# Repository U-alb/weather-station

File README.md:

# Weather Station

Rust-powered environmental monitoring station

## Description

The project builds a weather station which provides real-time weather data on an external display and web interface

## Motivation

Building a Raspberry Pi Pico W weather station with embassy-rs combined my interest in embedded systems with a chance to explore networking. It allows me to learn sensor interaction and data processing. Integrating a web interface adds a network layer, enabling real-time data display and opening doors for future functionalities like remote monitoring.

## Hardware

We will use a BME280 in order to gather environmental data. The Pico will process this gathered data in order to print meaningful graphics on the provided display. We will also use several push buttons in order to switch between the available data

### Bill of Materials

| Device | Usage | Price |
|--------|--------|-------|
| [Raspberry Pi Pico WH](https://www.raspberrypi.com/documentation/microcontrollers/raspberry-pi-pico.html) | The microcontroller | [56 RON](https://ardushop.ro/ro/home/2819-raspberry-pi-pico-wh.html) |
| [BME280](https://www.bosch-sensortec.com/products/environmental-sensors/humidity-sensors-bme280/) | Temperature, pressure and humidity sensor | [74 RON](https://www.optimusdigital.ro/ro/senzori-senzori-de-presiune/5649-modul-senzor-barometric-de-presiune-bme280.html) |
| [LED Display](https://ardushop.ro/8014-thickbox_default/modul-lcd-spi-128x160.webp) | Display | [39 RON](https://ardushop.ro/ro/home/2818-modul-lcd-spi-128x160.html) |
| [Breadboard](https://www.yamanelectronics.com/wp-content/uploads/2020/06/basics-of-breadboard.webp) | The physical base of the project | [10 RON](https://www.optimusdigital.ro/ro/prototipare-breadboard-uri/8-breadboard-830-points.html) |
| [Jumper Wires](http://www.atomsindustries.com/assets/images/items/1075/1075.webp) | For connecting all the different components | [7 RON](https://www.optimusdigital.ro/ro/fire-fire-mufate/886-set-fire-tata-tata-40p-15-cm.html) |
| [Push buttons](https://ardushop.ro/655-thickbox_default/buton-mic-push-button-trough-hole.webp) | For switching info on the screen| [0.36 RON each / 1.5 RON total](https://www.optimusdigital.ro/ro/butoane-i-comutatoare/1119-buton-6x6x6.html)

## Software

| Library | Description | Usage |
|---------|-------------|-------|
| [embassy-rp](https://github.com/embassy-rs/embassy/tree/main/embassy-rp) | The embassy-rp HAL targets the Raspberry Pi RP2040 microcontroller. The HAL implements both blocking and async APIs for many peripherals. |  The utilised HAL  |
| [embassy-sync](https://github.com/embassy-rs/embassy/tree/main/embassy-sync) | An Embassy project| Used for mutexes and sending and receiving data over channels |
| [embassy-time](https://github.com/embassy-rs/embassy/tree/main/embassy-time) | An Embassy project | Used for organising the flow of the program via Timer:: |
| [embassy-embedded-hal](https://github.com/embassy-rs/embassy/tree/main/embassy-embedded-hal) | Collection of utilities to use `embedded-hal` and `embedded-storage` traits with Embassy. | Used for the SPI config |
| [embassy-futures](https://github.com/embassy-rs/embassy/tree/main/embassy-futures) | An Embassy project | Used for working with futures during asynchronous development |
| [st7789](https://github.com/almindor/st7789) | Display driver for ST7789 | Used for the display |
| [embedded-graphics](https://github.com/embedded-graphics/embedded-graphics) | 2D graphics library | Used for drawing to the display |

## Links

1. [Idea](https://www.hackster.io/jotrinelectronics/building-a-weather-station-with-raspberry-pi-pico-rp2040-9d5cbb)
2. [Arduino BME280 Library (not Rust, but it was useful as a conceptual insight)](https://github.com/finitespace/BME280)

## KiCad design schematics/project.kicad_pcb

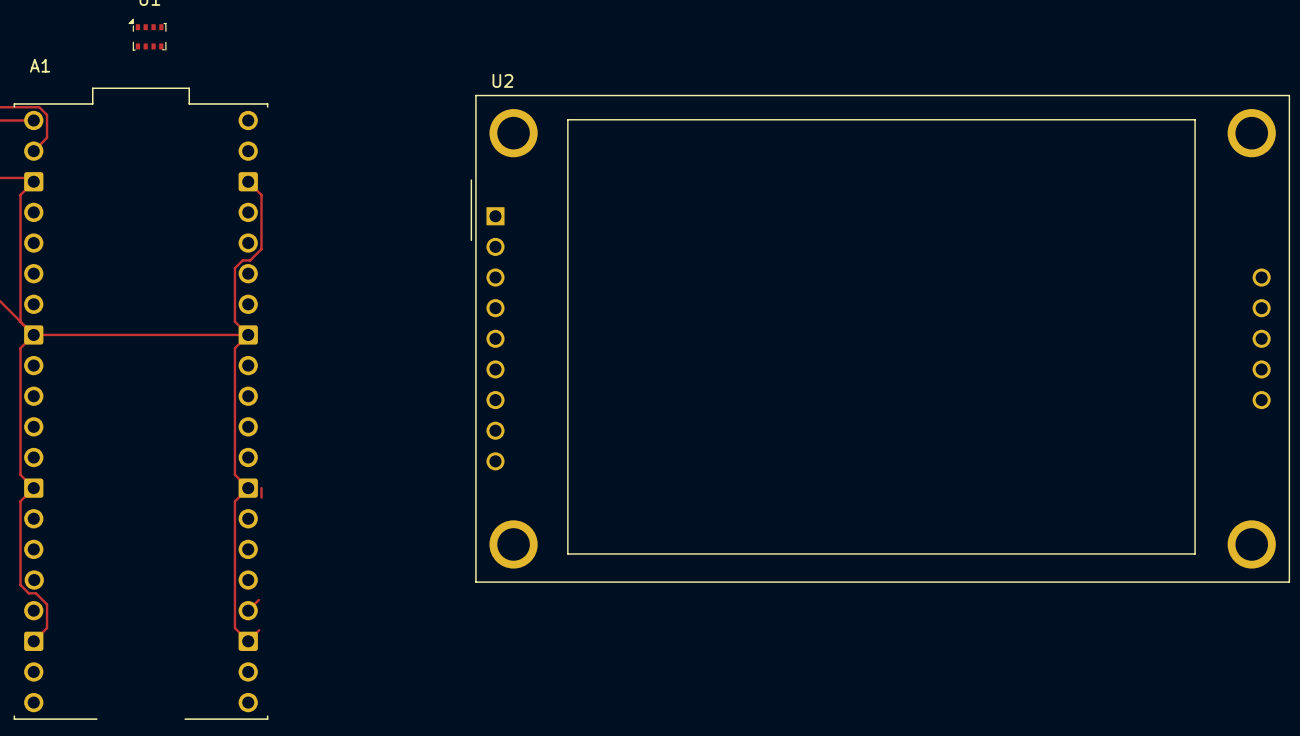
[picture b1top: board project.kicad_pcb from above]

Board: 2 copper layers, 3 parts (0 on the bottom side), 11 nets.

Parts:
A1: SC0918; MODULE_SC0918
U1: BMP280; Bosch_LGA-8_2x2.5mm_P0.65mm_ClockwisePinNumbering
U2: CR2013-MI2120

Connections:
+3V3: A1.36 (3V3_OUT), U1.6 (VDDIO), U1.8 (VDD), U2.1 (VCC), U2.8 (LED)
GND: A1.3 (GND), A1.8 (GND), A1.13 (GND), A1.18 (GND), A1.23 (GND), A1.28 (GND), A1.33 (AGND), A1.38 (GND), U1.1 (GND), U1.7 (GND), U2.2 (GND)
unnamed: A1.1 (GP0), U2.4 (RESET)
unnamed: A1.5 (GP3), U1.2 (CSB)
unnamed: A1.6 (GP4), U2.9 (MISO)
unnamed: A1.11 (GP8), U1.5 (SDO)
unnamed: A1.14 (GP10), U1.4 (SCK)
unnamed: A1.15 (GP11), U1.3 (SDI)
unnamed: A1.21 (GP16), U2.5 (D/~C)
unnamed: A1.22 (GP17), A1.25 (GP19), U2.3 (~CS), U2.6 (MOSI)
unnamed: A1.24 (GP18), U2.7 (SCK)

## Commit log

2025-03-31 Added the project files
